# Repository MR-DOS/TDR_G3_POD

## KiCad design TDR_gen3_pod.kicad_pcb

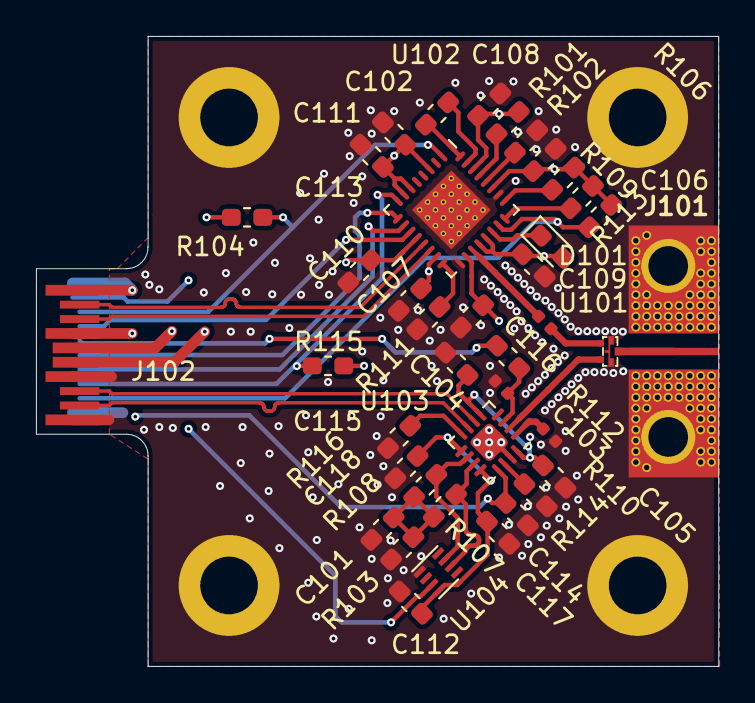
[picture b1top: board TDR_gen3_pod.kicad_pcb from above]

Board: 4 copper layers, 37.9 x 35.0 mm, 44 parts (0 on the bottom side), 35 nets.

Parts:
C101: 1n; C_0603_1608Metric_Pad1.05x0.95mm_HandSolder
C102: 1n/NC; C_0603_1608Metric_Pad1.05x0.95mm_HandSolder
C103: NA; C_0402_1005Metric
C104, C105, C106, C107, C108, C109, C110, C111, C112, C113, C114, C115, C117, C118: 10n; C_0603_1608Metric_Pad1.05x0.95mm_HandSolder
C116: 220p/NA; C_0402_1005Metric
D101: LED_TX; LED_0603_1608Metric_Pad1.05x0.95mm_HandSolder
H101, H103, H105, H106: MountingHole_Pad; MountingHole_3.2mm_M3_DIN965_Pad
J101: Conn_Coaxial; SMA_rosenberger_hybrid_ISOLA_2313_0.1mm
J102: SFP+; SFP+_PCB
R101, R102: 1k; R_0603_1608Metric_Pad1.05x0.95mm_HandSolder
R103, R107, R108, R116: 50; R_0603_1608Metric_Pad1.05x0.95mm_HandSolder
R104, R113, R115: 4k7; R_0603_1608Metric_Pad1.05x0.95mm_HandSolder
R106, R109: 400; R_0603_1608Metric_Pad1.05x0.95mm_HandSolder
R110: 50; R_0402_1005Metric
R111: 2k; R_0603_1608Metric_Pad1.05x0.95mm_HandSolder
R112: NA; R_0603_1608Metric_Pad1.05x0.95mm_HandSolder
R114: NC; R_0603_1608Metric_Pad1.05x0.95mm_HandSolder
U101: PS1608GT2-R50-T1; PS1608G
U102: MAX3798; QFN-32_EP_5x5_Pitch0.5mm
U103: ADCMP582; LFCSP-16-1EP_3x3mm_P0.5mm_EP1.6x1.6mm
U104: SY89321; LFCSP-8_2x2mm_P0.5mm

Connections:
+3V3: C106.1, C107.1, C108.1, C109.1, C110.1, C111.1, C112.1, C113.1, C115.2, C117.2, C118.2, D101.2, J102.16, R101.2, R104.2, R106.2, R109.2, R113.2, R115.2, U102.3, U102.6, U102.7, U102.12, U102.15, U102.18, U102.20, U102.21, U102.27, U102.30, U103.9, U103.12, U104.8
/COMP_OUT: J102.9, U104.7
/COMP_OUT_N: R108.2, U103.10, U104.3
/COMP_OUT_P: R107.2, U103.11, U104.2
/COMP_T: R110.2, U103.1
/COMP_VOLTAGE: J102.6, R112.1
/CSEL: J102.7, U102.11
/DISABLE: J102.3, R115.1, U102.8
/FAULT: J102.2, R113.1, U102.23
/LOS: J102.8, R104.1, U102.1
/PULSE_AC: C116.1, U101.3
/PULSE_GEN: C116.2, U102.19
/PULSE_N: J102.13, U102.14
/PULSE_P: J102.12, U102.13
/SAMPLE_N: J102.18, U103.6
/SAMPLE_P: J102.19, U103.7
/SCL: J102.5, U102.9
/SDA: J102.4, U102.10
/TDR_COMP: U101.2, U103.2
/TDR_PORT: J101.1, U101.1
/VCCR: C104.1, C105.1, J102.15, U103.5, U103.16
/VEER: C114.1, J102.10, J102.11, J102.14, U103.13
GND: C101.2, C103.1, C104.2, C105.2, C106.2, C107.2, C108.2, C109.2, C110.2, C111.2, C112.2, C113.2, C114.2, C115.1, C117.1, C118.1, H101.1, H103.1, H105.1, H106.1, J101.2, J102.1, J102.17, J102.20, R102.2, R103.1, R110.1, R111.2, R114.2, R116.2, U101.4, U102.17, U102.26, U102.33, U103.15, U103.17, U104.5
unnamed: C101.1, R103.2, R107.1, R108.1
unnamed: C102.1, U102.31
unnamed: C102.2, U102.32
unnamed: C103.2, R112.2, U103.3
unnamed: D101.1, U102.22
unnamed: R101.1, U102.29
unnamed: R102.1, U102.28
unnamed: R106.1, U102.25
unnamed: R109.1, U102.24
unnamed: R111.1, U102.16
unnamed: R114.1, U103.14
unnamed: R116.1, U103.8

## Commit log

2020-03-08 First commit, this version was sent to JLCPCB and will serve as first prototype.
2021-11-23 Create LICENSE
    Added GPLv3 license
